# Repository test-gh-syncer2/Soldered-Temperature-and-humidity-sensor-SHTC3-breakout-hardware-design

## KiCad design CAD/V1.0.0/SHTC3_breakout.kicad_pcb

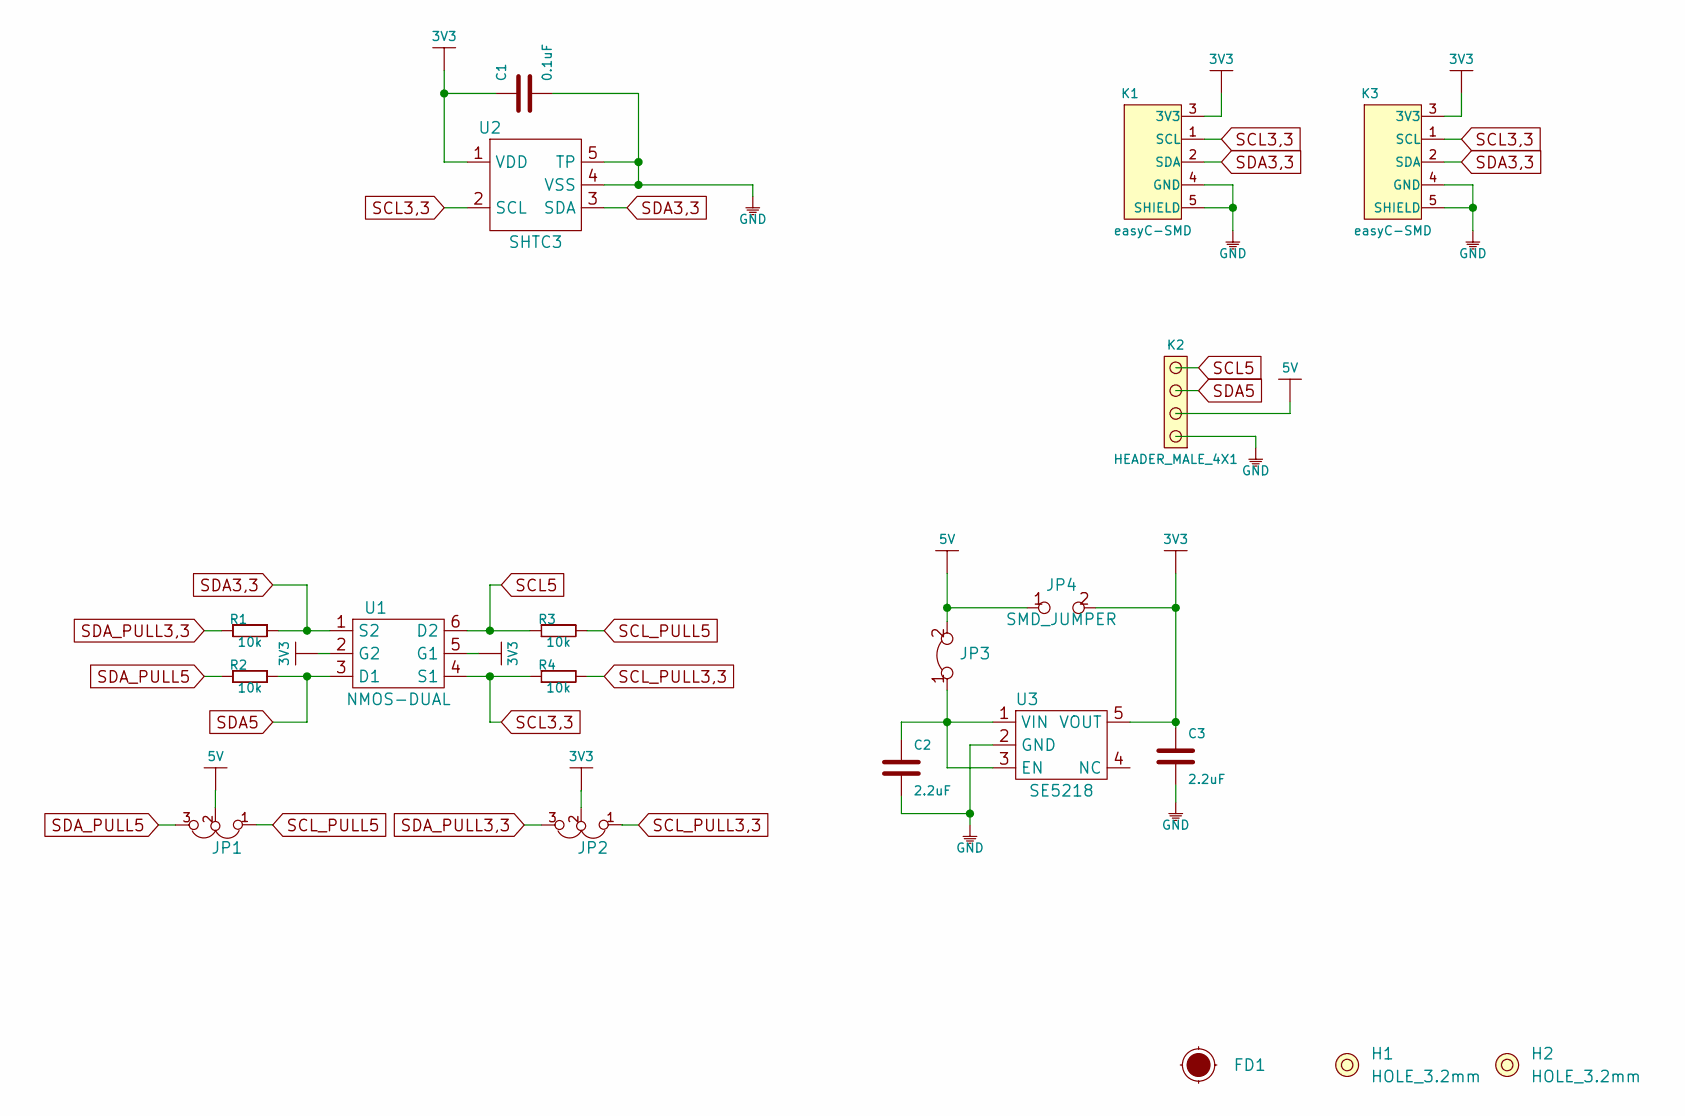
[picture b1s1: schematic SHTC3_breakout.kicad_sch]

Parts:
C1: 0.1uF; 0603C
C2, C3: 2.2uF; 0603C
FD1: Fiducial_Stencil; FIDUCIAL_1MM_PASTE
H1, H2: HOLE_3.2mm
JP1, JP2: SMD_JUMPER_3_PAD_TRACE
JP3: SMD-JUMPER-CONNECTED_TRACE_NOSLODERMASK
JP4: SMD_JUMPER
K1, K3: easyC-SMD; easyC-connector
K2: HEADER_MALE_4X1
R1, R2, R3, R4: 10k; 0603R
U1: NMOS-DUAL; SOT-363
U2: SHTC3
U3: SE5218; SOT-23-5

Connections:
3V3: C1.2, C3.2, JP2.2, JP4.2, K1.3 (3V3), K3.3 (3V3), U1.2 (G2), U1.5 (G1), U2.1 (VDD), U3.5 (VOUT)
5V: JP1.2, JP3.2, JP4.1, K2.2
GND: C1.1, C2.1, C3.1, K1.4 (GND), K1.5 (SHIELD), K2.1, K3.4 (GND), K3.5 (SHIELD), U2.4 (VSS), U2.5 (TP), U3.2 (GND)
unnamed: C2.2, JP3.1, U3.1 (VIN), U3.3 (EN)
SCL3,3: K1.1 (SCL), K3.1 (SCL), R4.1, U1.4 (S1), U2.2 (SCL)
SCL5: K2.4, R3.1, U1.6 (D2)
SCL_PULL3,3: JP2.1, R4.2
SCL_PULL5: JP1.1, R3.2
SDA3,3: K1.2 (SDA), K3.2 (SDA), R1.2, U1.1 (S2), U2.3 (SDA)
SDA5: K2.3, R2.2, U1.3 (D1)
SDA_PULL3,3: JP2.3, R1.1
SDA_PULL5: JP1.3, R2.1

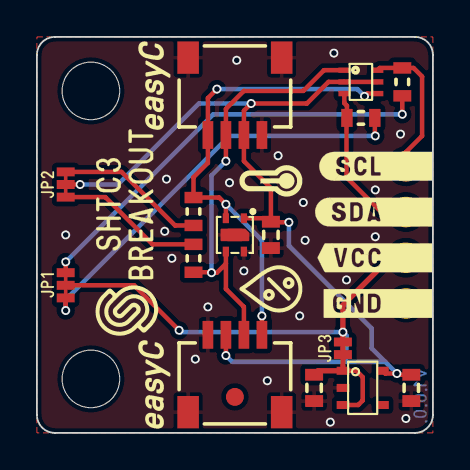
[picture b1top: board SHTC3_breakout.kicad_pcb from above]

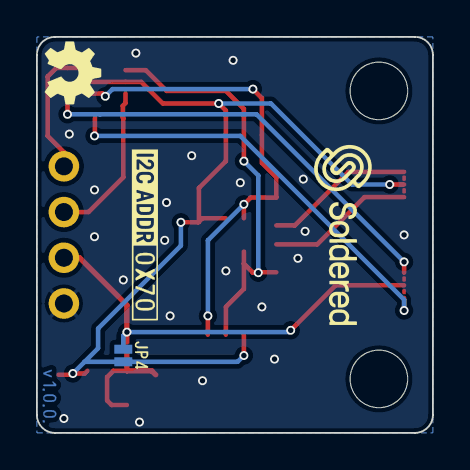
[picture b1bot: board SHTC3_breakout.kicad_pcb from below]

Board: 2 copper layers, 22.0 x 22.0 mm, 20 parts (2 on the bottom side), 12 nets.

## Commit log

2021-09-23 Syncing to git
2021-09-23 Updating open source files.
